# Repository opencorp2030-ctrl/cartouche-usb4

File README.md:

# CARTOUCHE Éclair V1 — a tiny USB4 NVMe drive for a local AI

CARTOUCHE is a way to store heavy AI models and run them easily and fast, while
keeping your data from going to third-party servers.

Website: [cartouche.candygate.eu](https://cartouche.candygate.eu/eclair.html)

| | |
|---|---|
| Board | 22.0 × 33.7 mm, 4 layers, 1.6 mm |
| USB4 controller | ASMedia ASM2464PD, 40 Gb/s, PCIe 4.0 x4 |
| Storage | M.2 2230 NVMe SSD, 256 GB – 2 TB |
| Case | aluminium, 25 × 65.7 × 15.6 mm with the cooling fins, laser-engraved, 3 colours |
| Expected speed | ≈ 3.5 GB/s on USB4 / Thunderbolt, ≈ 1 GB/s on USB 3.2 (not measured yet) |
| In the box | USB-C 40 Gb/s cable + USB-A cable |

| Full model | Inside (case transparent) |
|---|---|
|  |  |
| **Exploded view** | **Board + SSD** |
|  |  |
| **Cut through the middle** | **Underside, M3 screws** |
|  |  |

| PCB, top | PCB, bottom |
|---|---|
|  |  |

## Why I made this

I got the idea because I have a lot of other projects with AI, and this was a real
problem. I like solving the problems I have.

Why my own drive (Éclair) and not just USB keys: because I want it to be useful
for devs and to be a good deal. That's actually why I set up the developer program.

## Wiring

Full schematic: [`pcb/cartouche-usb4.kicad_sch`](pcb/cartouche-usb4.kicad_sch) ·
[PDF](docs/schematic.pdf)

## What's in the repository

| Folder | Content |
|---|---|
| [`BOM.csv`](BOM.csv) | every part, with manufacturer part numbers and supplier links that work from France |
| [`pcb/`](pcb) | KiCad 9 project (`.kicad_pro`, `.kicad_sch`, `.kicad_pcb`, symbol library), Gerbers + drills (`fab/cartouche-usb4-gerbers.zip`), pick-and-place, board STEP, import scripts |
| [`cad/`](cad) | **case source** (`eclair_v1.py`, CadQuery), and in `cad/out/`: case base and lid, SSD 2230 and USB-C plug (STEP + STL), the board as a printable mock-up (STL), and **`eclair_v1_assembly.step`, the full assembly with the electronics** |
| [`firmware/`](firmware) | how the drive enumerates (NVMe over USB4, UAS over USB 3), flashing the ASMedia firmware, `eclair_check.py` (link and speed check) |
| [`docs/`](docs) | [costs per unit](docs/COSTS.md), images |

## The case

The case will be made of good-quality aluminium, both to protect against shocks and
to get rid of the heat. It will be engraved so the info doesn't wear off over time.
Arranging everything as well as possible is pretty complicated. I'm really happy
with it, especially the purple colour of the case, which you can pick as an option
on the website.

| Part | Detail |
|---|---|
| Halves | base + lid, split under the board |
| Board + closing | 2 × M3 × 12 countersunk screws, from below, through the board's Ø3.2 holes into the lid |
| SSD | in the M.2 connector (LOTES APCI0113-P001A, 4.75 mm, since v1.3: the ARGOSY NASM0-S6701-TPH4 is out of stock): card 3.15 mm under the board, edge seated 1.75 mm past the connector posts (LOTES drawing AP-APCI0113, to confirm on the real part); M2 screw on a standoff of the base |
| Assembly order | plug the SSD into the board outside the case, press it flat, lay board + SSD into the base, M2 screw, then the lid |
| Rear | 1 × M2 × 10 screw |
| USB-C | receptacle flush with the front; plug model included, mated and checked |
| Cooling (passive, no fan) | lid boss + 1 mm thermal pad on the ASM2464PD; base boss + 1 mm thermal pad (20 × 22 mm) under the SSD; 5 fins under the base (1 mm). Leaves232 warns the ASM2464PD overheats and disconnects without cooling (he used a laptop fan): to be checked with a 15 min transfer on the aluminium prototype |
| Interference check | no overlap between board, SSD, plug, base and lid |
| Fit test | print `case_base.stl`, `case_lid.stl`, `ssd_2230.stl`, `board_mockup.stl` (the mock-up has a 1.0 mm card slot cut in the connector); values to confirm are marked `CHECK` in `eclair_v1.py` |
| Fit check (CadQuery) | 0 mm³ overlap between SSD, board, case base, lid and USB-C plug |

The chart is an estimate from a simple thermal-resistance model (assumptions under the chart), not a measurement.

## Éclair Dock (optional): under the desk

| Top: Éclair slides in | Desk side: rails, screw bosses, air slots |
|---|---|
|  |  |

| Part | Detail |
|---|---|
| Size | 29.9 × 73.8 × 27.2 mm, CNC aluminium, polished |
| Mounting | 2 countersunk wood screws Ø4 under the desk (reachable with Éclair out) |
| Holding Éclair | Éclair hangs upside down on two lips (engraved lid facing the room), 0.25 mm clearance, 14 mm sticks out to grip it |
| Cable | USB4 40 Gb/s 0.8 m cable, its plug clamped in the rear block (plate + 4 × M2 countersunk): sliding Éclair in plugs it, pulling it out unplugs it |
| Airflow | 2 rails + 2 bosses keep the plate 5 mm off the desk; slots above the fins let warm air out along that gap (see diagram) |
| Fit check (CadQuery) | 0 mm³ overlap between dock, clamp, case and plug |
| Files | `cad/out/dock_body.step/.stl`, `dock_clamp.step/.stl`, `eclair_dock_assembly.step` (with the electronics) |

**Installing it**: a 1:1 drilling template is in [`docs/dock-drilling-template.pdf`](docs/dock-drilling-template.pdf) (print at 100 %, check the 50 mm bar; generated from the CAD numbers by `cad/make_dock_template.py`). Pilot holes Ø2.5 × 14 mm, desk top 18 mm thick minimum.

**Print test**: print `cad/out/dock_body.stl` (rails flat on the bed), `dock_clamp.stl`, `case_base.stl` and `case_lid.stl` in PLA/PETG, 0.2 mm layers. The 0.25 mm clearance is meant for machined aluminium; on an FDM print, sand the lips lightly if Éclair rubs.

3D films of the dock (object, installation, everyday use, cooling): https://cartouche.candygate.eu/support.html

## Credit: what is mine and what is not

For this prototype, I'd rather start from something that works, even if I have to
adjust it, than start again from zero (no need to reinvent the wheel). All the
ideas, the tests and the code are my work ;)

| From [Leaves232/2230-USB4-SSD-Enclosure-Design](https://github.com/Leaves232/2230-USB4-SSD-Enclosure-Design) (MIT, see [`LICENSE-upstream-MIT`](LICENSE-upstream-MIT)) | Mine |
|---|---|
| schematic, component placement, USB4/PCIe routing (not modified) | KiCad 9 conversion and fab package, smallest outline, case CAD, SSD and cable fit, BOM with suppliers and costs, flashing procedure and check tool, the CARTOUCHE software |

Schematic imported from the original Altium project into KiCad 9
(`pcb/cartouche-usb4.kicad_sch`, symbols in `pcb/ASM2464PD-altium-import.kicad_sym`).

## How to get it made

| Board parameter | Value |
|---|---|
| Layers / material | 4 layers, FR-4 TG150, 1.6 mm |
| Finish / copper | ENIG, 1 oz outer / 0.5 oz inner |
| Impedance | 85 Ω differential pairs on the outer layers |
| Track / space, vias | 3.5 / 3.5 mil, 0.2 mm tented vias |
| Assembly | by the fab (ASM2464PD = 0.46 mm pitch BGA) |
| Copper zones | do not refill in KiCad (from the tested original) |

1. Order the board assembled (PCBA).
2. Plug the SSD, place the thermal pad.
3. Screw the board and SSD into the base, close the lid.
4. Flash the firmware once ([`firmware/`](firmware)).

## Status

We're working on testing our own Éclair boards, and then, why not, making a sort of
mini computer you plug into your PC that runs the model on its own RAM and its own
storage.

## Licence

MIT, like the original design. See [`LICENSE`](LICENSE) and
[`LICENSE-upstream-MIT`](LICENSE-upstream-MIT).

## Bill of materials

Same content as [`BOM.csv`](BOM.csv).

| # | Qty | Value | Package | Manufacturer | Part number | Unit price | Link |
|---|---|---|---|---|---|---|---|
| 1 | 3 | 22uF | C0402 | Samsung | GRM155R60J226ME11D | CNY 0.22275 | [link](https://www.lcsc.com/search?q=GRM155R60J226ME11D) |
| 2 | 15 | 10uF | C0402 | Samsung | CL05A106MQ5NUNC | CNY 0.02281 | [link](https://www.lcsc.com/search?q=CL05A106MQ5NUNC) |
| 3 | 26 | 2.2uf | C0402 | Samsung | CL05A225KP5NSNC | CNY 0.01346 | [link](https://www.lcsc.com/search?q=CL05A225KP5NSNC) |
| 4 | 16 | 100nF | C0402 | FH | 0402F104M500NT | CNY 0.00481 | [link](https://www.lcsc.com/search?q=0402F104M500NT) |
| 5 | 1 | 1uF | C0402 | FH | 0402X105K6R3NT | CNY 0.00766 | [link](https://www.lcsc.com/search?q=0402X105K6R3NT) |
| 6 | 12 | 220nF | C0201 | Murata | GRM033R60J224ME15D | CNY 0.00917 | [link](https://www.lcsc.com/search?q=GRM033R60J224ME15D) |
| 7 | 1 | 20pF | C0402 | Yageo | CC0402JRNPO9BN200 | CNY 0.00456 | [link](https://www.lcsc.com/search?q=CC0402JRNPO9BN200) |
| 8 | 4 | 330nF | C0201 | Murata | GRM033R60J334ME90D | CNY 0.05114 | [link](https://www.lcsc.com/search?q=GRM033R60J334ME90D) |
| 9 | 2 | 220pF | C0402 | FH | 0402B221K500NT | CNY 0.00433 | [link](https://www.lcsc.com/search?q=0402B221K500NT) |
| 10 | 2 | 30pF | C0402 | FH | 0402CG300J500NT | CNY 0.00454 | [link](https://www.lcsc.com/search?q=0402CG300J500NT) |
| 11 | 1 | 4.7pf | C0402 | FH | 0402CG4R7B500NT | CNY 0.00744 | [link](https://www.lcsc.com/search?q=0402CG4R7B500NT) |
| 12 | 1 | 6.8pf | C0402 | FH | 0402CG6R8C500NT | CNY 0.00420 | [link](https://www.lcsc.com/search?q=0402CG6R8C500NT) |
| 13 | 1 | 33u | C0402 | Murata | GRM155R60J226ME11D | CNY 0.67700 | [link](https://www.lcsc.com/search?q=GRM155R60J226ME11D) |
| 14 | 1 | 3.3nf | C0402 | FH | 0402B332K500NT | CNY 0.00382 | [link](https://www.lcsc.com/search?q=0402B332K500NT) |
| 15 | 1 | 330uF | CAP-SMD_L7.3-W4.3-R-RD | Panasonic | 6TPE330MAP | CNY 2.37008 | [link](https://www.lcsc.com/search?q=6TPE330MAP) |
| 16 | 1 | M.2-MKEY CONNECTOR | CONN-SMD_APCI0113-P001A | LOTES | APCI0113-P001A (H4.8) | USD 0.74 | [link](https://www.lcsc.com/product-detail/C841669.html) |
| 17 | 2 | 1uh | IND-SMD_L2.0-W1.6-B | cjiang | FTC201610S1R0MBCA | CNY 0.19611 | [link](https://www.lcsc.com/search?q=FTC201610S1R0MBCA) |
| 18 | 1 | Red LED 0402 | LED0402-RD | Everlight | 16-213SDRC/S530-A3/TR8 | see link | [link](https://www.lcsc.com/product-detail/C71911.html) |
| 19 | 5 | 4.7K 1% | R0402 | Uniohm | 0402WGF4701TCE | CNY 0.00219 | [link](https://www.lcsc.com/search?q=0402WGF4701TCE) |
| 20 | 1 | 12.1K 1% | R0402 | Uniohm | 0402WGF1212TCE | CNY 0.00212 | [link](https://www.lcsc.com/search?q=0402WGF1212TCE) |
| 21 | 3 | 100K 1% | R0402 | Uniohm | 0402WGF1003TCE | CNY 0.00200 | [link](https://www.lcsc.com/search?q=0402WGF1003TCE) |
| 22 | 2 | 0 | R0402 | Uniohm | 0402WGF0000TCE | CNY 0.00198 | [link](https://www.lcsc.com/search?q=0402WGF0000TCE) |
| 23 | 1 | 1K 1% | R0402 | Uniohm | 0402WGF1001TCE | CNY 0.00222 | [link](https://www.lcsc.com/search?q=0402WGF1001TCE) |
| 24 | 5 | 10K 1% | R0402 | Uniohm | 0402WGF1002TCE | CNY 0.00216 | [link](https://www.lcsc.com/search?q=0402WGF1002TCE) |
| 25 | 8 | 220K 1% | R0201 | Uniohm | 0201WMF2203TEE | CNY 0.00446 | [link](https://www.lcsc.com/search?q=0201WMF2203TEE) |
| 26 | 1 | 140K 1% | R0402 | Yageo | RC0402FR-07140KL | CNY 0.00279 | [link](https://www.lcsc.com/search?q=RC0402FR-07140KL) |
| 27 | 1 | 261K 1% | R0402 | UniOhm | 0402WGF2613TCE | CNY 0.00216 | [link](https://www.lcsc.com/search?q=0402WGF2613TCE) |
| 28 | 1 | 475K 1% | R0402 | Yageo | RC0402FR-07475KL | CNY 0.00446 | [link](https://www.lcsc.com/search?q=RC0402FR-07475KL) |
| 29 | 1 | 150K 1% | R0402 | Uniohm | 0402WGF1503TCE | CNY 0.00213 | [link](https://www.lcsc.com/search?q=0402WGF1503TCE) |
| 30 | 1 | LTC3315AEV#TRPBF | LQFN-12_L2.0-W2.0-P0.50-TL-EP0.7 | ADI | LTC3315AEV#TRPBF | CNY 16.64280 | [link](https://www.lcsc.com/search?q=LTC3315AEV%23TRPBF) |
| 31 | 1 | ASM2464PD | BGA-273 0.46 mm | ASMedia | ASM2464PD | USD 26.60 (Alibaba, 1-99 pcs) | [link](https://jlcpcb.com/partdetail/Asmedia-ASM2464PD/C7509569) |
| 32 | 1 | TPS82130SILR | USIP-8_L3.0-W2.8-P0.65-TL-EP | TI | TPS82130SILR | CNY 22.94600 | [link](https://www.lcsc.com/search?q=TPS82130SILR) |
| 33 | 1 | SIP32408DNP-T1-GE4 | SIP32408DNP-T1-GE4 | Vishay | SIP32408DNP-T1-GE4 | CNY 4.50360 | [link](https://www.lcsc.com/search?q=SIP32408DNP-T1-GE4) |
| 34 | 1 | ZD25WQ16CEIGR | USON-8_L3.0-W2.0-P0.50-BL-EP | Zetta(澜智) | ZD25WQ16CEIGR | CNY 1.02600 | [link](https://www.lcsc.com/search?q=ZD25WQ16CEIGR) |
| 35 | 1 | 105450-0101 | USB-C-SMD_TYPE-C-USB-18 | Molex | 105450-0101 | CNY 6.32500 | [link](https://www.lcsc.com/search?q=105450-0101) |
| 36 | 1 | 25MHz | CRYSTAL-SMD_4P-L1.6-W1.2-BL | YXC | X322525MSB4SI | CNY 0.29520 | [link](https://www.lcsc.com/search?q=X322525MSB4SI) |
| 37 | 1 | M.2 2230 NVMe SSD, PCIe 4.0, 256 GB – 2 TB | M.2 2230 M-key | Western Digital / Kioxia / Corsair | SN740 / BG6 / MP600 Mini | EUR 30–130 | [link](https://www.amazon.fr/s?k=ssd+m.2+2230+nvme) |
| 38 | 2 | M3 x 12 countersunk (ISO 10642) |  |  |  | ≈ EUR 0.10 | [link](https://www.amazon.fr/s?k=vis+M3+12mm+tete+fraisee) |
| 39 | 1 | M2 x 10 countersunk |  |  |  | ≈ EUR 0.10 | [link](https://www.amazon.fr/s?k=vis+M2+10mm+tete+fraisee) |
| 40 | 1 | M2 x 3 (M.2 SSD screw) |  |  |  | ≈ EUR 0.10 | [link](https://www.amazon.fr/s?k=vis+m.2+ssd+kit) |
| 41 | 1 | 1 mm, ≥ 12 W/mK, cut 10 x 10 mm (chip) + 20 x 22 mm (SSD) |  |  |  | ≈ EUR 0.40 | [link](https://www.amazon.fr/s?k=pad+thermique+1mm+12w) |
| 42 | 1 | case_base + case_lid (cad/out) | aluminium CNC anodised, or 3D print for tests |  |  | ≈ EUR 15–35 | [link](https://jlccnc.com) |
| 43 | 1 | USB-C to USB-C, USB4 40 Gb/s, 0.5 m |  | UGREEN or equivalent |  | ≈ EUR 15 | [link](https://www.amazon.fr/s?k=cable+usb4+40gbps+0.5m) |
| 44 | 1 | USB-A to USB-C, 10 Gb/s, 0.5 m |  |  |  | ≈ EUR 10 | [link](https://www.amazon.fr/s?k=cable+usb+a+usb+c+10gbps+0.5m) |
| 45 | 1 | Éclair Dock, CNC aluminium, polished (cad/out/dock_body.step) |  |  |  | ≈ EUR 35 | [link](https://jlccnc.com) |
| 46 | 1 | cable clamp plate (cad/out/dock_clamp.step) |  |  |  | ≈ EUR 5 | [link](https://jlccnc.com) |
| 47 | 1 | USB-C to USB-C, USB4 40 Gb/s, 0.8 m |  |  |  | ≈ EUR 15 | [link](https://www.amazon.fr/s?k=cable+usb4+40gbps+0.8m) |
| 48 | 2 | countersunk Ø4 × 16 |  |  |  | ≈ EUR 0.20 | [link](https://www.amazon.fr/s?k=vis+bois+tete+fraisee+4x16) |
| 49 | 4 | M2 × 5 countersunk |  |  |  | ≈ EUR 0.20 | [link](https://www.amazon.fr/s?k=vis+m2+fraisee) |
| **TOTAL** |  | **One CARTOUCHE Éclair V1 256 GB, all parts + case + cables + box (batch of 10)** |  |  |  | **≈ EUR 149.00** | [docs/COSTS.md](docs/COSTS.md) |
| **TOTAL** |  | **Éclair V1 256 GB + Éclair Dock** |  |  |  | **≈ EUR 206.50** | [docs/COSTS.md](docs/COSTS.md) |

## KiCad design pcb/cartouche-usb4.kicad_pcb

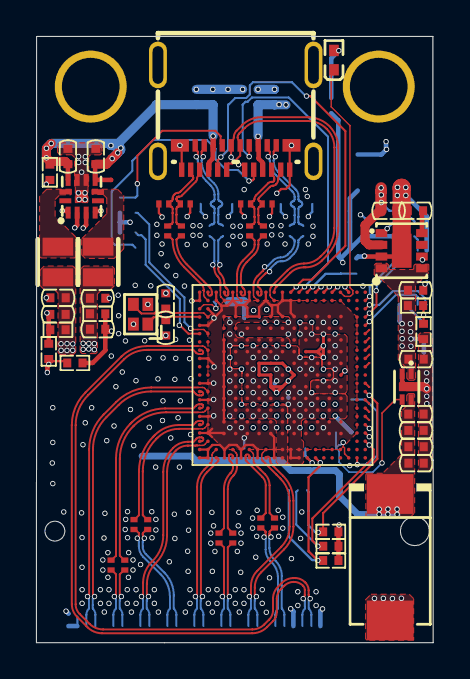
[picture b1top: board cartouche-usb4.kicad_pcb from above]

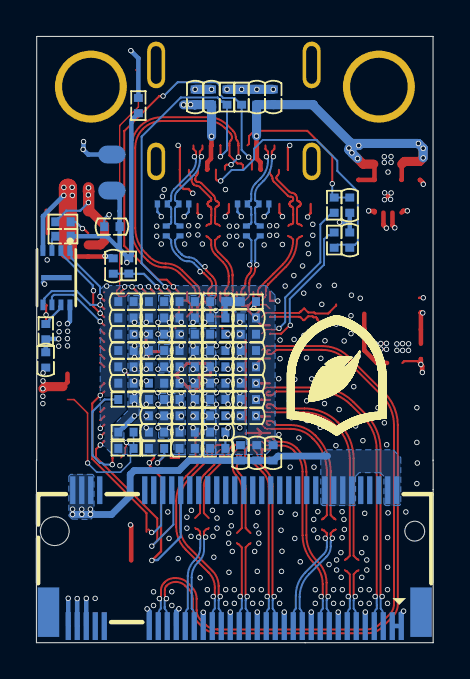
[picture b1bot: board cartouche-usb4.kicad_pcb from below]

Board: 4 copper layers, 22.0 x 33.7 mm, 134 parts (80 on the bottom side), 82 nets.

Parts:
C1, C3, C6, C10, C12, C15, C17, C19, C22, C24, C26, C28, C29, C30, C32, C33, C35, C36, C37, C38, C39, C41, C42, C44, C45, C47: 2.2u; C0402
C2, C5, C9, C11, C14, C18, C21, C25, C27, C31, C61, C66, C67, C70, C71, C76: 100n; C0402
C4, C8, C13, C16, C20, C23, C40, C43, C46, C51, C57, C103, C104, C109: 10u; C0402
C7, C102: 22u; C0402
C34: 1u; C0402
C48, C49, C50, C52, C53, C54, C55, C56, C64, C65, C74, C75: 220n; C0201
C59: 20p; C0402
C62, C63, C72, C73: 330n; C0201
C68, C69: 220p; C0402
C77, C78: 30p; C0402
C100: 10uF; C0402
C101: 4.7pf; C0402
C105: 6.8pf; C0402
C106: 33u; C0402
C107: 3.3nf; C0402
C108: 22uf; C0402
CE1: 330uF; CAP-SMD_L7.3-W4.3-R-RD
CN1: M.2-MKEY CONNECTOR; CONN-SMD_APCI0113-P001A
J17, J18: ?HDR1x1; Header
L5, L6: 1uh; IND-SMD_L2.0-W1.6-B
LED1: 19-217/R6C-AL1M2VY/3T; LED0402-RD
R1, R2, R3, R33, R34: 4.7K 1%; R0402
R4: 12.1K 1%; R0402
R6, R104, R106: 100K 1%; R0402
R12, R13: 0; R0402
R14, R16: 2M /NC; R0402
R19: 100K /NC; R0402
R20: 1K 1%; R0402
R21, R22, R23, R103, R110: 10K 1%; R0402
R24, R25, R26, R27, R28, R29, R30, R31: 220K 1%; R0201
R105: 140K 1%; R0402
R107: 261K 1%; R0402
R108: 475K 1%; R0402
R109: 150K 1%; R0402
TP1, TP2: tpc60t_68
U01: LTC3315AEV#TRPBF; LQFN-12_L2.0-W2.0-P0.50-TL-EP0.7
U2: ASM2464PD; BGA273C46P21X21_1000X1000X98
U02: TPS82130SILR; USIP-8_L3.0-W2.8-P0.65-TL-EP
U4: SIP32408DNP-T1-GE4
U31: ZD25WQ16CEIGR; USON-8_L3.0-W2.0-P0.50-BL-EP
USBC1: 105450-0101; USB-C-SMD_TYPE-C-USB-18
X1: 25MHz; CRYSTAL-SMD_4P-L1.6-W1.2-BL

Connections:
1.1V: C1.1, C2.1, C10.1, C11.1, C17.1, C18.1, C24.1, C25.1, C29.1, C32.1, C35.1, C37.1, C39.1, C40.1, C42.1, C43.1, C45.1, C46.1, C105.2, C106.2, L5.2, R105.1, U2.D14, U2.D16, U2.E11, U2.E14, U2.E16, U2.F9, U2.F11, U2.F14, U2.F16, U2.H9, U2.H11, U2.H13, U2.H14, U2.H16, U2.J8, U2.J9, U2.J13, U2.J14, U2.J16, U2.J17, U2.J18, U2.J20, U2.J21, U2.K20, U2.K21, U2.L8, U2.L11, U2.L14, U2.N8, U2.N14, U2.P8, U2.P13, U2.P14, U2.T8, U2.T9, U2.T11, U2.T13, U2.T14, U2.U8, U2.U9
1.8V: C3.1, C4.1, C12.1, C13.1, C19.1, C20.1, C26.1, C30.1, C33.1, C36.1, C38.1, C41.1, C44.1, C47.1, C101.2, C102.2, L6.1, R107.2, U2.L6, U2.L16, U2.L17, U2.L18, U2.L20, U2.L21, U2.N6, U2.N16, U2.P6, U2.P16, U2.T6, U2.T16, U2.U6, U2.U11, U2.U13, U2.U14, U2.U16
3.3V: C5.1, C6.1, C7.1, C14.1, C15.1, C21.1, C22.1, C27.1, C28.1, C31.1, C61.1, C76.2, C100.1, C108.2, R1.1, R2.1, R6.2, R19.2, R21.2, R22.2, R23.2, R33.1, R34.1, R108.1, TP1.1, U02.4, U02.5, U2.D6, U2.D8, U2.D9, U2.D13, U2.E6, U2.E8, U2.E9, U2.E13, U2.F6, U2.F13, U2.H5, U2.H6, U4.1, U31.8
3.3V_M.2: C8.1, C9.1, C16.1, C23.1, C51.1, C57.1, C59.1, CE1.1, CN1.2, CN1.4, CN1.12, CN1.14, CN1.16, CN1.18, CN1.70, CN1.72, CN1.74, U4.4
CC11: C69.1, R12.1, USBC1.A5
CC21: C68.2, R13.1, USBC1.B5
GND: C1.2, C2.2, C3.2, C4.2, C5.2, C6.2, C7.2, C8.2, C9.2, C10.2, C11.2, C12.2, C13.2, C14.2, C15.2, C16.2, C17.2, C18.2, C19.2, C20.2, C21.2, C22.2, C23.2, C24.2, C25.2, C26.2, C27.2, C28.2, C29.2, C30.2, C31.2, C32.2, C33.2, C34.1, C35.2, C36.2, C37.2, C38.2, C39.2, C40.2, C41.2, C42.2, C43.2, C44.2, C45.2, C46.2, C47.2, C51.2, C57.2, C59.2, C61.2, C66.1, C67.2, C68.1, C69.2, C70.1, C71.2, C76.1, C77.2, C78.2, C100.2, C102.1, C103.1, C104.1, C106.1, C107.1, C108.1, C109.1, CE1.2, CN1.1, CN1.3, CN1.9, CN1.15, CN1.21, CN1.27, CN1.33, CN1.39, CN1.45, CN1.51, CN1.57, CN1.71, CN1.73, CN1.75, J17.1, J18.1, R3.2, R4.2, R14.1, R16.1, R20.1, R24.1, R25.2, R26.1, R27.2, R28.1, R29.2, R30.1, R31.2, R104.2, R106.1, R109.2, TP2.1, U01.8, U01.9, U01.13, U02.3, U02.9, U2.AA1, U2.AA2, U2.AA5, U2.AA9, U2.AA12, U2.AA14, U2.AA16, U2.AA18, U2.AA20, U2.AA21, U2.D4, U2.D5, U2.D11, U2.D17, U2.D18, U2.E4, U2.E5, U2.E17, U2.E18, U2.F4, U2.F5, U2.F8, U2.F17, U2.F18, U2.H4, U2.H8, U2.H17, U2.H18, U2.J4, U2.J5, U2.J6, U2.J11, U2.K2, U2.L1, U2.L2, U2.L4, U2.L5, U2.L9, U2.L13, U2.M20, U2.M21, U2.N1, U2.N2, U2.N4, U2.N5, U2.N9, U2.N11, U2.N13, U2.N17, U2.N18, U2.P4, U2.P5, U2.P9, U2.P11, U2.P17, U2.P18, U2.P20, U2.P21, U2.R1, U2.R2, U2.T4, U2.T5, U2.T17, U2.T18, U2.T20, U2.T21, U2.U1, U2.U2, U2.U4, U2.U5, U2.U17, U2.U18, U2.V4, U2.V5, U2.V6, U2.V8, U2.V9, U2.V11, U2.V13, U2.V14, U2.V16, U2.V17, U2.V18, U2.V20, U2.V21, U2.W1, U2.W2, U2.Y3, U2.Y5, U2.Y9, U2.Y12, U2.Y14, U2.Y16, U2.Y18, U2.Y20, U2.Y21, U4.2, U4.5, U31.4, U31.9, USBC1.0, USBC1.A1, USBC1.A12, USBC1.B1, USBC1.B12, X1.2, X1.4
GPIO0: LED1.2, U2.D1
GPIO8: CN1.52, R22.1, U2.A19
GPIO22: CN1.54, R23.1, U2.A13
HDDPC: R19.1, R20.2, U2.C21, U4.3
NetC101_1: C101.1, R106.2, R107.1, U01.3
NetC105_1: C105.1, R104.1, R105.2, U01.2
NetC107_2: C107.2, U02.8
NetL5_1: L5.1, U01.11
NetL6_2: L6.2, U01.6
NetLED1_1: LED1.1, R2.2
NetR12_2: R12.2, U2.AA6
NetR13_2: R13.2, U2.Y6
NetR33_2: R33.2, U31.7
NetR103_1: R103.1, U01.1, U01.4
NetR108_2: R108.2, R109.1, U02.6
NetR110_2: R110.2, U02.1
PER0_N: CN1.41, U2.N20
PER0_P: CN1.43, U2.N21
PER1_N: CN1.29, U2.W20
PER1_P: CN1.31, U2.W21
PER2_N: CN1.17, U2.AA19
PER2_P: CN1.19, U2.Y19
PER3_N: CN1.5, U2.Y13
PER3_P: CN1.7, U2.AA13
PERST_B: CN1.50, R21.1, U2.G21
PET0U_N: C55.2, CN1.47
PET0U_P: C56.2, CN1.49
PET0_N: C55.1, U2.R21
PET0_P: C56.1, U2.R20
PET1U_N: C53.2, CN1.35
PET1U_P: C54.2, CN1.37
PET1_N: C53.1, U2.U21
PET1_P: C54.1, U2.U20
PET2U_N: C50.2, CN1.23
PET2U_P: C52.2, CN1.25
PET2_N: C50.1, U2.AA17
PET2_P: C52.1, U2.Y17
PET3U_N: C48.2, CN1.11
PET3U_P: C49.2, CN1.13
PET3_N: C48.1, U2.AA15
PET3_P: C49.1, U2.Y15
RST: C34.2, R6.1, U2.H1
RefCLK_N: CN1.53, U2.Y8
RefCLK_P: CN1.55, U2.AA8
SBU1: R14.2, U2.K1, USBC1.A8
SBU2: R16.2, U2.J1, USBC1.B8
SPI_CLK: U2.A5, U31.6
SPI_CS#: U2.A2, U31.1
SPI_DI: U2.A4, U31.2
SPI_DO: U2.A3, U31.5
TEST_EN: R3.1, U2.H21
UART_TX: R1.2, U2.B21
UD_N: U2.M2, USBC1.A7, USBC1.B7
UD_P: U2.M1, USBC1.A6, USBC1.B6
UREXT: R4.1, U2.AA3
URX0_CON_N: C63.1, R28.2, USBC1.B10
URX0_CON_P: C62.1, R30.2, USBC1.B11
URX0_N: C63.2, U2.P2
URX0_P: C62.2, U2.P1
URX1_CON_N: C72.1, R27.1, USBC1.A10
URX1_CON_P: C73.1, R25.1, USBC1.A11
URX1_N: C72.2, U2.Y1
URX1_P: C73.2, U2.Y2
UTX0_CON_N: C65.1, R29.1, USBC1.A3
UTX0_CON_P: C64.1, R31.1, USBC1.A2
UTX0_N: C65.2, U2.T2
UTX0_P: C64.2, U2.T1
UTX1_CON_N: C74.1, R26.2, USBC1.B3
UTX1_CON_P: C75.1, R24.2, USBC1.B2
UTX1_N: C74.2, U2.V1
UTX1_P: C75.2, U2.V2
VBUS1: C66.2, C67.1, C70.2, C71.1, C103.2, C104.2, C109.2, R103.2, R110.1, U01.7, U01.10, U02.2, U2.G1, USBC1.A4, USBC1.A9, USBC1.B4, USBC1.B9
WP: R34.2, U31.3
XI: C78.1, U2.AA4, X1.1
XO: C77.1, U2.Y4, X1.3

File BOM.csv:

Item,Qty per unit,Reference,Value,Package,Manufacturer,Manufacturer part number,Supplier link (ships to France),Unit price,Bought by,Note
1,3,"C7, C102,C108",22uF,C0402,Samsung,GRM155R60J226ME11D,https://www.lcsc.com/search?q=GRM155R60J226ME11D,CNY 0.22275,assembler (turnkey PCBA),
2,15,"C4, C8, C13, C16, C20, C23, C40, C43, C46, C51, C57, C103, C104, C109,C100",10uF,C0402,Samsung,CL05A106MQ5NUNC,https://www.lcsc.com/search?q=CL05A106MQ5NUNC,CNY 0.02281,assembler (turnkey PCBA),
3,26,"C1, C3, C6, C10, C12, C15, C17, C19, C22, C24, C26, C28, C29, C30, C32, C33, C35, C36, C37, C38, C39, C41, C42, C44, C45, C47",2.2uf,C0402,Samsung,CL05A225KP5NSNC,https://www.lcsc.com/search?q=CL05A225KP5NSNC,CNY 0.01346,assembler (turnkey PCBA),
4,16,"C2, C5, C9, C11, C14, C18, C21, C25, C27, C31, C61, C66, C67, C70, C71, C76",100nF,C0402,FH,0402F104M500NT,https://www.lcsc.com/search?q=0402F104M500NT,CNY 0.00481,assembler (turnkey PCBA),
5,1,C34,1uF,C0402,FH,0402X105K6R3NT,https://www.lcsc.com/search?q=0402X105K6R3NT,CNY 0.00766,assembler (turnkey PCBA),
6,12,"C48, C49, C50, C52, C53, C54, C55, C56, C64, C65, C74, C75",220nF,C0201,Murata,GRM033R60J224ME15D,https://www.lcsc.com/search?q=GRM033R60J224ME15D,CNY 0.00917,assembler (turnkey PCBA),
7,1,C59,20pF,C0402,Yageo,CC0402JRNPO9BN200,https://www.lcsc.com/search?q=CC0402JRNPO9BN200,CNY 0.00456,assembler (turnkey PCBA),
8,4,"C62, C63, C72, C73",330nF,C0201,Murata,GRM033R60J334ME90D,https://www.lcsc.com/search?q=GRM033R60J334ME90D,CNY 0.05114,assembler (turnkey PCBA),
9,2,"C68, C69",220pF,C0402,FH,0402B221K500NT,https://www.lcsc.com/search?q=0402B221K500NT,CNY 0.00433,assembler (turnkey PCBA),
10,2,"C77, C78",30pF,C0402,FH,0402CG300J500NT,https://www.lcsc.com/search?q=0402CG300J500NT,CNY 0.00454,assembler (turnkey PCBA),
11,1,C101,4.7pf,C0402,FH,0402CG4R7B500NT,https://www.lcsc.com/search?q=0402CG4R7B500NT,CNY 0.00744,assembler (turnkey PCBA),
12,1,C105,6.8pf,C0402,FH,0402CG6R8C500NT,https://www.lcsc.com/search?q=0402CG6R8C500NT,CNY 0.00420,assembler (turnkey PCBA),
13,1,C106,33u,C0402,Murata,GRM155R60J226ME11D,https://www.lcsc.com/search?q=GRM155R60J226ME11D,CNY 0.67700,assembler (turnkey PCBA),
14,1,C107,3.3nf,C0402,FH,0402B332K500NT,https://www.lcsc.com/search?q=0402B332K500NT,CNY 0.00382,assembler (turnkey PCBA),
15,1,CE1,330uF,CAP-SMD_L7.3-W4.3-R-RD,Panasonic,6TPE330MAP,https://www.lcsc.com/search?q=6TPE330MAP,CNY 2.37008,assembler (turnkey PCBA),
16,1,CN1,M.2-MKEY CONNECTOR,CONN-SMD_APCI0113-P001A,ARGOSY,NASM0-S6701-TPH4,https://www.lcsc.com/search?q=NASM0-S6701-TPH4,CNY 1.41750,assembler (turnkey PCBA),
17,2,"L5, L6",1uh,IND-SMD_L2.0-W1.6-B,cjiang,FTC201610S1R0MBCA,https://www.lcsc.com/search?q=FTC201610S1R0MBCA,CNY 0.19611,assembler (turnkey PCBA),
18,1,LED1,19-217/R6C-AL1M2VY/3T,LED0402-RD,Everlight,19-217/R6C-AL1M2VY/6T,https://www.lcsc.com/search?q=19-217/R6C-AL1M2VY/6T,CNY 0.07979,assembler (turnkey PCBA),
19,5,"R1, R2, R3, R33, R34",4.7K 1%,R0402,Uniohm,0402WGF4701TCE,https://www.lcsc.com/search?q=0402WGF4701TCE,CNY 0.00219,assembler (turnkey PCBA),
20,1,R4,12.1K 1%,R0402,Uniohm,0402WGF1212TCE,https://www.lcsc.com/search?q=0402WGF1212TCE,CNY 0.00212,assembler (turnkey PCBA),
21,3,"R6, R104, R106",100K 1%,R0402,Uniohm,0402WGF1003TCE,https://www.lcsc.com/search?q=0402WGF1003TCE,CNY 0.00200,assembler (turnkey PCBA),
22,2,"R12, R13",0,R0402,Uniohm,0402WGF0000TCE,https://www.lcsc.com/search?q=0402WGF0000TCE,CNY 0.00198,assembler (turnkey PCBA),
23,1,R20,1K 1%,R0402,Uniohm,0402WGF1001TCE,https://www.lcsc.com/search?q=0402WGF1001TCE,CNY 0.00222,assembler (turnkey PCBA),
24,5,"R21, R22, R23, R103, R110",10K 1%,R0402,Uniohm,0402WGF1002TCE,https://www.lcsc.com/search?q=0402WGF1002TCE,CNY 0.00216,assembler (turnkey PCBA),
25,8,"R24, R25, R26, R27, R28, R29, R30, R31",220K 1%,R0201,Uniohm,0201WMF2203TEE,https://www.lcsc.com/search?q=0201WMF2203TEE,CNY 0.00446,assembler (turnkey PCBA),
26,1,R105,140K 1%,R0402,Yageo,RC0402FR-07140KL,https://www.lcsc.com/search?q=RC0402FR-07140KL,CNY 0.00279,assembler (turnkey PCBA),
27,1,R107,261K 1%,R0402,UniOhm,0402WGF2613TCE,https://www.lcsc.com/search?q=0402WGF2613TCE,CNY 0.00216,assembler (turnkey PCBA),
28,1,R108,475K 1%,R0402,Yageo,RC0402FR-07475KL,https://www.lcsc.com/search?q=RC0402FR-07475KL,CNY 0.00446,assembler (turnkey PCBA),
29,1,R109,150K 1%,R0402,Uniohm,0402WGF1503TCE,https://www.lcsc.com/search?q=0402WGF1503TCE,CNY 0.00213,assembler (turnkey PCBA),
30,1,U01,LTC3315AEV#TRPBF,LQFN-12_L2.0-W2.0-P0.50-TL-EP0.7,ADI,LTC3315AEV#TRPBF,https://www.lcsc.com/search?q=LTC3315AEV%23TRPBF,CNY 16.64280,assembler (turnkey PCBA),
31,1,U2,ASM2464PD,BGA-273 0.46 mm,ASMedia,ASM2464PD,https://jlcpcb.com/partdetail/Asmedia-ASM2464PD/C7509569,"USD 26.60 (Alibaba, 1-99 pcs)",assembler (or consigned),USB4 to PCIe 4.0 x4 bridge
32,1,U02,TPS82130SILR,USIP-8_L3.0-W2.8-P0.65-TL-EP,TI,TPS82130SILR,https://www.lcsc.com/search?q=TPS82130SILR,CNY 22.94600,assembler (turnkey PCBA),
33,1,U4,SIP32408DNP-T1-GE4,SIP32408DNP-T1-GE4,Vishay,SIP32408DNP-T1-GE4,https://www.lcsc.com/search?q=SIP32408DNP-T1-GE4,CNY 4.50360,assembler (turnkey PCBA),
34,1,U31,ZD25WQ16CEIGR,USON-8_L3.0-W2.0-P0.50-BL-EP,Zetta(澜智),ZD25WQ16CEIGR,https://www.lcsc.com/search?q=ZD25WQ16CEIGR,CNY 1.02600,assembler (turnkey PCBA),
35,1,USBC1,105450-0101,USB-C-SMD_TYPE-C-USB-18,Molex,105450-0101,https://www.lcsc.com/search?q=105450-0101,CNY 6.32500,assembler (turnkey PCBA),
36,1,X1,25MHz,CRYSTAL-SMD_4P-L1.6-W1.2-BL,YXC,X322525MSB4SI,https://www.lcsc.com/search?q=X322525MSB4SI,CNY 0.29520,assembler (turnkey PCBA),
37,1,SSD,"M.2 2230 NVMe SSD, PCIe 4.0, 256 GB – 2 TB",M.2 2230 M-key,Western Digital / Kioxia / Corsair,SN740 / BG6 / MP600 Mini,https://www.amazon.fr/s?k=ssd+m.2+2230+nvme,EUR 30–130,maker,plugs in by hand
38,2,Screws,M3 x 12 countersunk (ISO 10642),,,,https://www.amazon.fr/s?k=vis+M3+12mm+tete+fraisee,≈ EUR 0.10,maker,base + board + lid (board holes Ø3.2)
39,1,Screw,M2 x 10 countersunk,,,,https://www.amazon.fr/s?k=vis+M2+10mm+tete+fraisee,≈ EUR 0.10,maker,rear closing screw
40,1,Screw,M2 x 3 (M.2 SSD screw),,,,https://www.amazon.fr/s?k=vis+m.2+ssd+kit,≈ EUR 0.10,maker,holds the SSD on the standoff
41,1,Thermal pad,"1 mm, ≥ 12 W/mK, cut 10 x 10 mm",,,,https://www.amazon.fr/s?k=pad+thermique+1mm+12w,≈ EUR 0.40,maker,between the ASM2464PD and the lid boss
42,1,Case,case_base + case_lid (cad/out),"aluminium CNC anodised, or 3D print for tests",,,https://jlccnc.com,≈ EUR 15–35,maker,laser-engraved lid
43,1,Cable,"USB-C to USB-C, USB4 40 Gb/s, 0.5 m",,UGREEN or equivalent,,https://www.amazon.fr/s?k=cable+usb4+40gbps+0.5m,≈ EUR 15,maker,full speed
44,1,Cable,"USB-A to USB-C, 10 Gb/s, 0.5 m",,,,https://www.amazon.fr/s?k=cable+usb+a+usb+c+10gbps+0.5m,≈ EUR 10,maker,computers without USB-C
